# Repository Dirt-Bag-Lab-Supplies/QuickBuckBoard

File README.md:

# QuickBuckBoard
Switching Regulator with 0.1" header for quick use on breadboard or on pcb

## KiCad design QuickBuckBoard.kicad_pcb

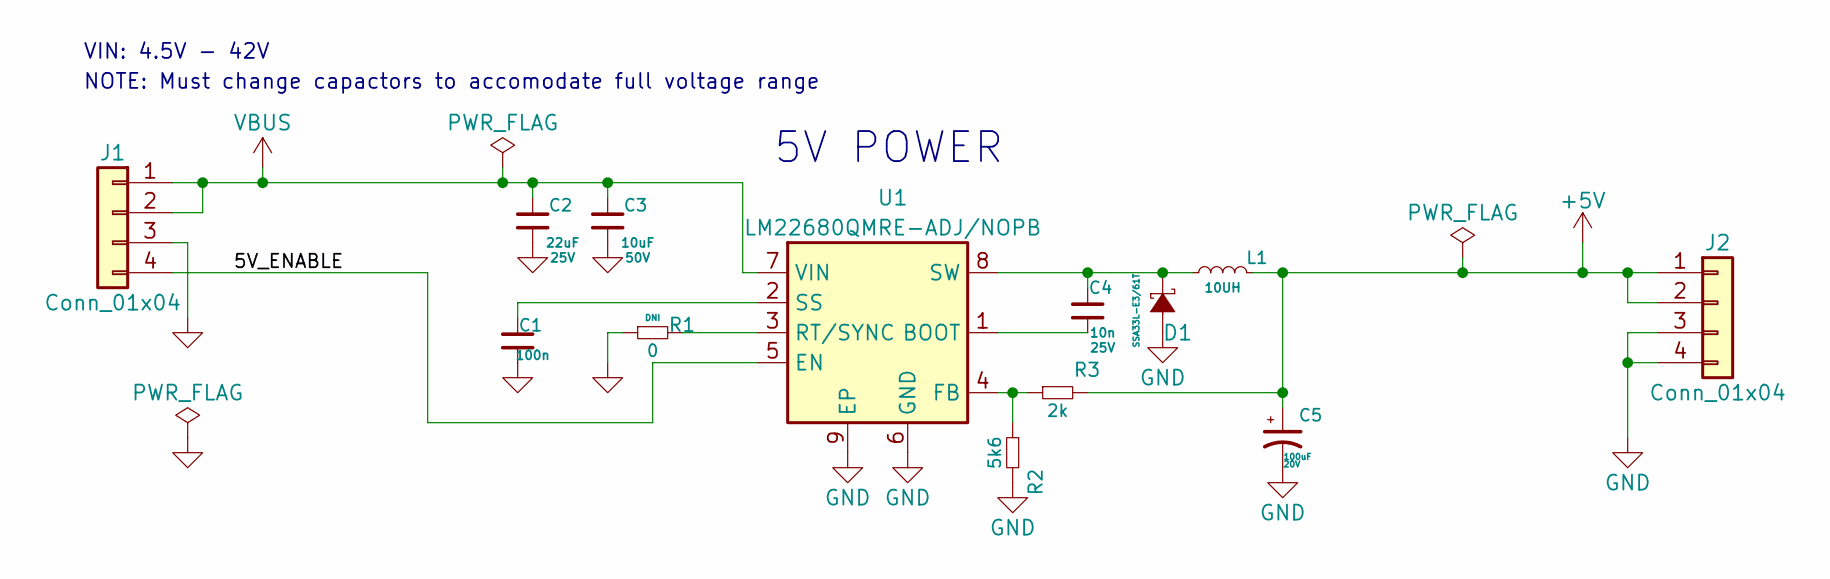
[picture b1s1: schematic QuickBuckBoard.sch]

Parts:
C1: MURATA_GCM155R71C104KA55J; C_0402; mfg_pn GCM155R71C104KA55J
C2: MURATA_GRM31CC81E226KE11L; C_1206; voltage 25V; mfg_pn GRM31CC81E226KE11L
C3: MURATA_GRT31CR61H106KE01L; C_1206; voltage 50V; mfg_pn GRT31CR61H106KE01L
C4: MURATA_GCM155R71E103KA37D; C_0402; voltage 25V; mfg_pn GCM155R71E103KA37D
C5: VISHAY_593D107X0020E2TE3; C_2917; voltage 20V; mfg_pn 593D107X0020E2TE3
D1: VISHAY_SSA33L-E3_61T; D_SMA; mfg_pn SSA33L-E3/61T
J1, J2: Conn_01x04; Pin_Header_Straight_1x04_Pitch2.54mm
L1: PANASONIC_ETQ-P3M100KVN; L_6.4x6.0_H3; mfg_pn ETQ-P3M100KVN
R1: VISHAYDALE_CRCW04020000Z0EDHP; R_0402; mfg_pn CRCW04020000Z0EDHP
R2: VISHAYDALE_CRCW04025K60JNED; R_0402; mfg_pn CRCW04025K60JNED
R3: VISHAYDALE_CRCW04022K00JNEDC; R_0402; mfg_pn CRCW04022K00JNEDC
U1: TI_LM22680QMRE-ADJ; SOIC-8-1EP_3.9x4.9mm_Pitch1.27mm_ALT; mfg_pn LM22680QMRE-ADJ/NOPB

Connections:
+5V: C5.1, J2.1, J2.2, L1.2, R3.2
/5V_ENABLE: J1.4, U1.5 (EN)
GND: C1.2, C2.2, C3.2, C5.2, D1.2 (A), J1.3, J2.3, J2.4, R1.1, R2.2, U1.6 (GND), U1.9 (EP)
unnamed: C1.1, U1.2 (SS)
unnamed: C4.1, D1.1 (K), L1.1, U1.8 (SW)
unnamed: C4.2, U1.1 (BOOT)
unnamed: R1.2, U1.3 (RT/SYNC)
unnamed: R2.1, R3.1, U1.4 (FB)
VBUS: C2.1, C3.1, J1.1, J1.2, U1.7 (VIN)

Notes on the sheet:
5V POWER
VIN: 4.5V - 42V
NOTE: Must change capactors to accomodate full voltage range

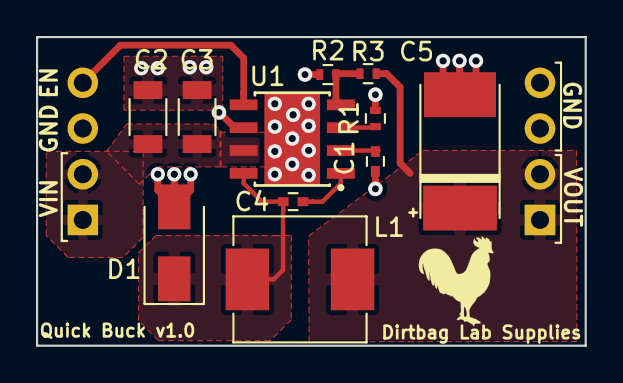
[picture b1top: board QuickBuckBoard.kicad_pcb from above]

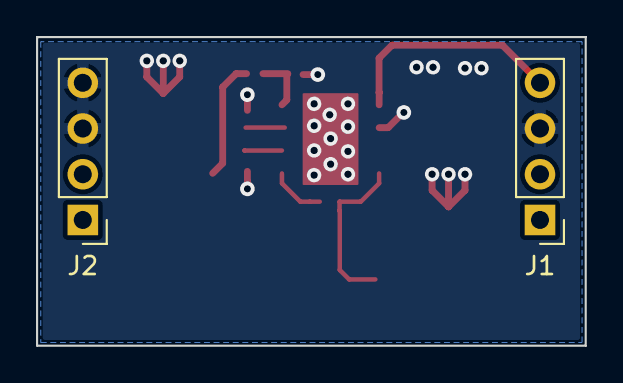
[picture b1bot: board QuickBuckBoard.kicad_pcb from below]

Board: 2 copper layers, 30.5 x 17.1 mm, 13 parts (2 on the bottom side), 9 nets.

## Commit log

2021-10-14 First commit with schematic/pcb
2021-10-14 First draft layout
